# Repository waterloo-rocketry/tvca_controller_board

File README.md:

# TVCA Controller Board

This repository contains both the kicad files used to design the TVCA controller board and the firmware.

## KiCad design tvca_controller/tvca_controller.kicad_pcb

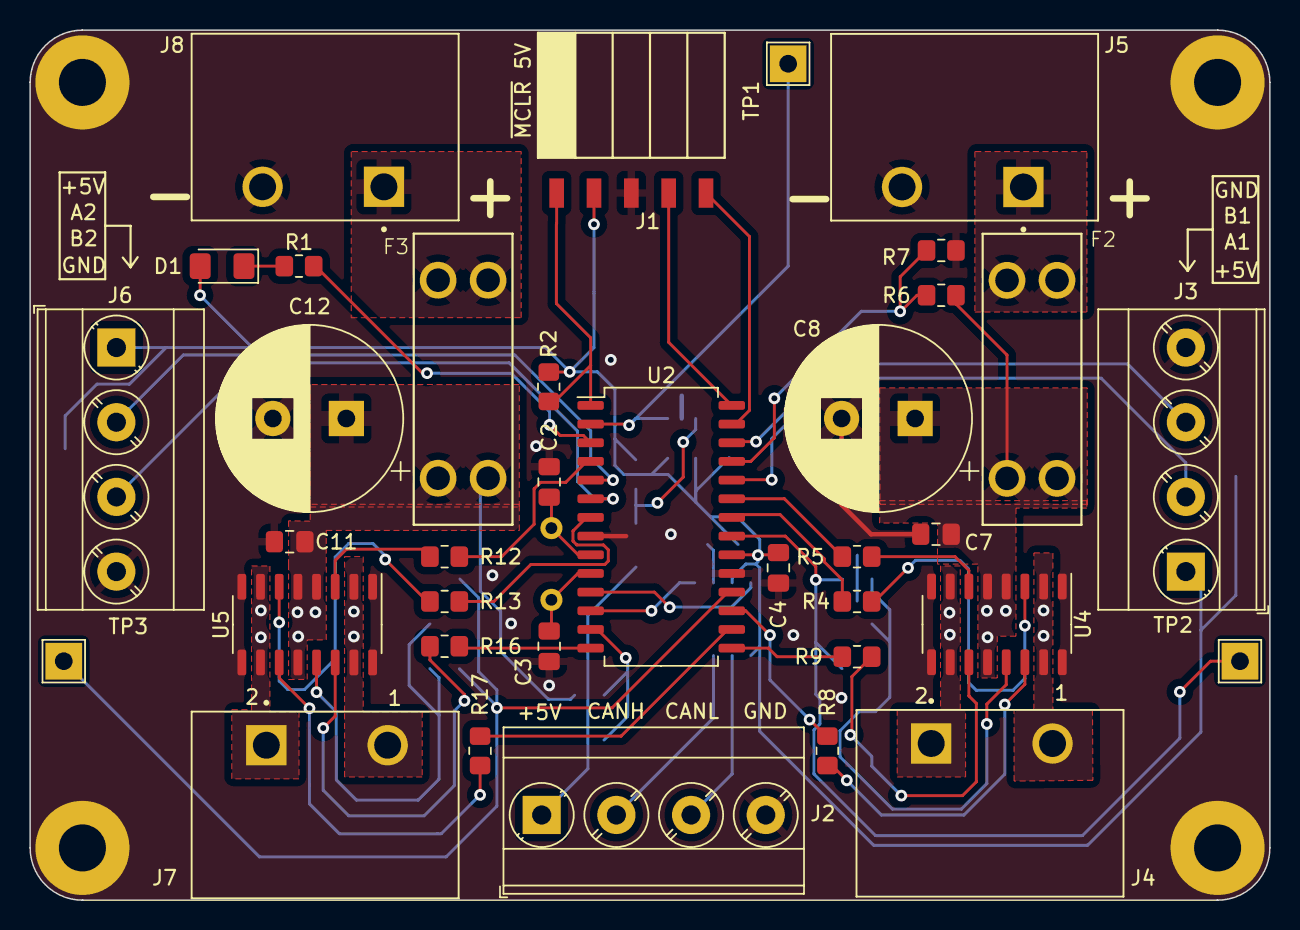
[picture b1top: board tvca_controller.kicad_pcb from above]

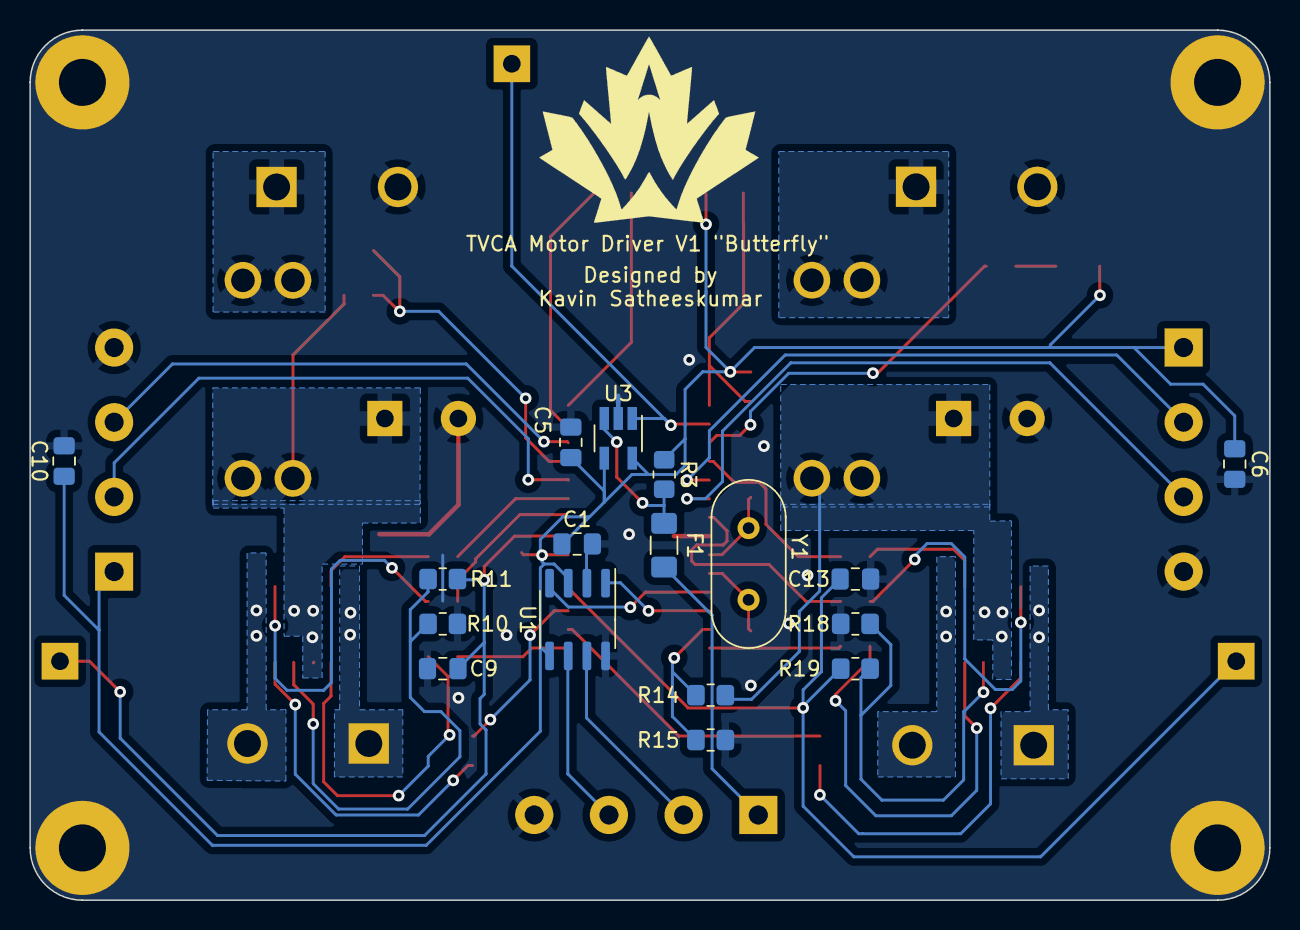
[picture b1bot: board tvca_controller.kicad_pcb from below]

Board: 2 copper layers, 84.3 x 59.2 mm, 57 parts (17 on the bottom side), 50 nets.

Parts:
C1: 10uF; C_0805_2012Metric_Pad1.18x1.45mm_HandSolder
C2, C3: 27pF; C_0805_2012Metric_Pad1.18x1.45mm_HandSolder
C4, C5, C6, C10: 0.1uF; C_0805_2012Metric_Pad1.18x1.45mm_HandSolder
C7, C11: 100nF; C_0805_2012Metric_Pad1.18x1.45mm_HandSolder
C8, C12: 270uF; CP_Radial_D12.5mm_P5.00mm
C9, C13: 10nF; C_0805_2012Metric_Pad1.18x1.45mm_HandSolder
D1: RED; LED_1206_3216Metric_Pad1.42x1.75mm_HandSolder
F1: 350mA; Fuse_1206_3216Metric_Pad1.42x1.75mm_HandSolder
F2, F3: 25A; Fuseholder_36-3557-15-ND
H1, H2, H3, H4: Mount; MountingHole_3.2mm_M3_Pad
J1: Programming Header; PinSocket_5x2.54_SMD_90deg_952-3198-1-ND
J2, J3, J6: PT 1,5/ 4-5,0-H; TerminalBlock_Phoenix_MKDS-3-4-5.08_1x04_P5.08mm_Horizontal
J4, J5, J7, J8: 4DB-P108-02; TE_2-1437667-4
R1: 330R; R_0805_2012Metric_Pad1.20x1.40mm_HandSolder
R2, R11, R19: 10k; R_0805_2012Metric_Pad1.20x1.40mm_HandSolder
R3: 200mR 1%; R_0805_2012Metric_Pad1.20x1.40mm_HandSolder
R4, R5, R8, R9, R12, R13, R16, R17: 1k; R_0805_2012Metric_Pad1.20x1.40mm_HandSolder
R6, R14: 21.5k 1%; R_0805_2012Metric_Pad1.20x1.40mm_HandSolder
R7, R15: 10k 1%; R_0805_2012Metric_Pad1.20x1.40mm_HandSolder
R10, R18: 866R 1%; R_0805_2012Metric_Pad1.20x1.40mm_HandSolder
TP1: 5V current draw; TestPoint_THTPad_2.5x2.5mm_Drill1.2mm
TP2, TP3: TestPoint; TestPoint_THTPad_2.5x2.5mm_Drill1.2mm
U1: MCP2562; SOIC-8_3.9x4.9mm_P1.27mm
U2: PIC18F26K83; SOIC-28W_7.5x18.7mm_P1.27mm
U3: INA180; SOT-23-5_HandSoldering
U4, U5: VNH7070AS; SO-16_3.9x9.9mm_P1.27mm
Y1: Crystal 12 MHz; Crystal_HC49-4H_Vertical

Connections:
+5V: C1.1, C4.1, C5.1, C6.1, C10.1, D1.2 (A), J1.2, J3.1, J6.1, R2.1, R3.1, U1.3 (VDD), U1.5 (VIO), U2.20 (VDD), U3.4 (IN-), U3.5 (VS)
/CANH: J2.2, U1.7 (CANH)
/CANL: J2.3, U1.6 (CANL)
/CAN_RX: U1.4 (RXD), U2.11 (RC0)
/CAN_TX: U1.1 (TXD), U2.12 (RC1)
/CCW_1: R5.2, U2.23 (RB2)
/CCW_2: R13.2, U2.7 (RA5)
/CLW_1: R4.2, U2.22 (RB1)
/CLW_2: R12.2, U2.4 (RA2)
/CUR_1: C9.1, R11.1, TP2.1, U2.21 (RB0)
/CUR_2: C13.1, R19.1, TP3.1, U2.18 (RC7)
/CUR_AMP: TP1.1, U2.2 (RA0), U3.1 (VO)
/ENCDRA_1: J3.2, U2.24 (RB3)
/ENCDRA_2: J6.2, U2.5 (RA3)
/ENCDRB_1: J3.3, U2.26 (RB5)
/ENCDRB_2: J6.3, U2.6 (RA4)
/ICSPCLK: J1.5, U2.27 (RB6/ICSPCLK)
/ICSPDAT: J1.4, U2.28 (RB7/ICSPDAT)
/Motor_1/OUT_1: J4.2, U4.2 (OUT_A), U4.15 (OUT_A)
/Motor_1/OUT_2: J4.1, U4.7 (OUT_B), U4.10 (OUT_B)
/Motor_1/POWER: C7.1, C8.1, F2.2, R6.1, U4.4 (VCC), U4.5 (VCC), U4.12 (VCC)
/Motor_2/OUT_1: J7.2, U5.2 (OUT_A), U5.15 (OUT_A)
/Motor_2/OUT_2: J7.1, U5.7 (OUT_B), U5.10 (OUT_B)
/Motor_2/POWER: C11.1, C12.1, F3.2, R14.1, U5.4 (VCC), U5.5 (VCC), U5.12 (VCC)
/OSC1: C2.1, U2.9 (RA7/OSC1), Y1.1
/OSC2: C3.1, U2.10 (RA6/OSC2), Y1.2
/PWM_1: R9.1, U2.15 (RC4)
/PWM_2: R17.1, U2.16 (RC5)
/SEL_1: R8.1, U2.17 (RC6)
/SEL_2: R16.1, U2.14 (RC3)
/VBAT_1: R6.2, R7.1, U2.25 (RB4)
/VBAT_2: R14.2, R15.1, U2.13 (RC2)
/~MCLR: J1.1, R2.2, U2.1 (~MCLR)
GND: C1.2, C2.2, C3.2, C4.2, C5.2, C6.2, C7.2, C8.2, C9.2, C10.2, C11.2, C12.2, C13.2, H1.1, H2.1, H3.1, H4.1, J1.3, J2.4, J3.4, J5.2, J6.4, J8.2, R7.2, R10.2, R15.2, R18.2, U1.2 (VSS), U1.8 (STBY), U2.8 (VSS), U2.19 (VSS), U3.2 (GND), U4.1 (GND_A), U4.8 (GND_B), U4.9 (GND_B), U4.16 (GND_A), U5.1 (GND_A), U5.8 (GND_B), U5.9 (GND_B), U5.16 (GND_A)
unnamed: D1.1 (K), R1.2
unnamed: F1.1, J2.1
unnamed: F2.1, J5.1
unnamed: F3.1, J8.1
unnamed: R1.1, U2.3 (RA1)
unnamed: F1.2, R3.2, U3.3 (IN+)
unnamed: R10.1, R11.2, U4.13 (CS)
unnamed: R4.1, U4.3 (IN_A)
unnamed: R5.1, U4.6 (IN_B)
unnamed: R9.2, U4.11 (PWM)
unnamed: R8.2, U4.14 (SEL_0)
unnamed: R18.1, R19.2, U5.13 (CS)
unnamed: R12.1, U5.3 (IN_A)
unnamed: R13.1, U5.6 (IN_B)
unnamed: R17.2, U5.11 (PWM)
unnamed: R16.2, U5.14 (SEL_0)

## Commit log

2024-05-14 inital commit
2024-05-14 README.md
2024-05-14 remove schematic
2024-05-14 tiny ass random change to ensure I can do git stuff
2024-06-06 get basic motor control logic going
2024-06-16 add can connector, and git ignore
2024-06-17 remove zips, refactor PCB to use software in place of 2-bit mux
2024-06-18 add connectors
2024-06-19 add current and voltage sensing. Address minor fixes suggested by Jack. Ready for final review
2024-07-05 Add foot prints, numerous other small changes
2024-07-05 shize shunt resistor
2024-07-10 Finish up schematic for jack to review, start PCB layout
2024-07-19 Replace motor controller IC
2024-07-20 remove kicad_prl
2024-07-24 Update motor controller IC and fuse holders
2024-07-29 Various nit-picks
2024-07-30 new footprint
2024-07-31 Get started on PCB layout
2024-07-31 Move the pic a bit
2024-07-31 Fix screw terminal
2024-08-03 Calculate R sense
2024-08-03 Fix units/R-sense calculation
2024-08-04 New PCB layout
2024-08-07 address a set of comments
2024-08-09 finalize layout
2024-08-10 add final layout and edge cuts
2024-08-14 High power routing
2024-08-14 small fix
2024-08-28 routing
2024-08-29 Address routing comments
2024-09-05 Various small fixes
2024-09-06 Add team logo, a bunch of lables, and my name
2024-09-06 Fix some silkscreens
2024-09-09 finish silkscreen
2024-09-11 Make +/- bigger
2024-09-13 move IC's over
2024-09-13 Rio's comments
2024-09-13 remove wierd corner ground things
2024-09-13 add ground via
